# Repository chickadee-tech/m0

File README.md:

# Chickadee Tech M0 Polystack Control Board #
This control board features an ARM cortex M0 based SAMD21, the same chip as the Arduino Zero, and will be Arduino-compatible.

## Documentation ##
See the [wiki](https://github.com/chickadee-tech/m0/wiki) for documentation.

## Polystack ##
This **control** board is part of the Polystack platform for modular microcontrol systems. More information on the platform can be found at [polystack.org](http://polystack.org).

## Support ##
If you need support with a board you own or have development questions please email support@chickadee.tech or check [chickadee.tech/support](https://chickadee.tech/support) for other ways to get support.

## Contributing ##
Please note that this project is released with a [Contributor Code of Conduct](CODE_OF_CONDUCT.md). By participating in this project you agree to abide by its terms.

### Setup ###
Components and footprints for PCB parts are not included in this repository. Instead, checkout the [chickadee-tech/kicad-libs](https://github.com/chickadee-tech/kicad-libs) repository in the same directory that this repository is checked out in. All part definitions should be relative so that they will load correctly.

### Pull requests ###
For fixes please submit a pull request to the original repository. After the pull request is merged, check the [Chickadee Tech Active Contributor Discount (ACD)](https://chickadee.tech/active-contributor) to see if you are eligible for a discount code to use on your next purchase.

### Derivatives ###
If developing your own version of the M0 board please remove all Chickadee Tech trademarks and follow the [CC-BY license](LICENSE). While not required, please consider open sourcing your modifications so others can learn from your improvements. If you do email support@chickadee.tech and we may choose to add your project to the ACD.

You may also license the Polystack logo for free by emailing support@chickadee.tech. We'll ask for your gerbers to ensure the design complies with specifications laid out [here](https://github.com/chickadee-tech/polystack/wiki) and provide written permission to use the trademark after compliance has been demonstrated.

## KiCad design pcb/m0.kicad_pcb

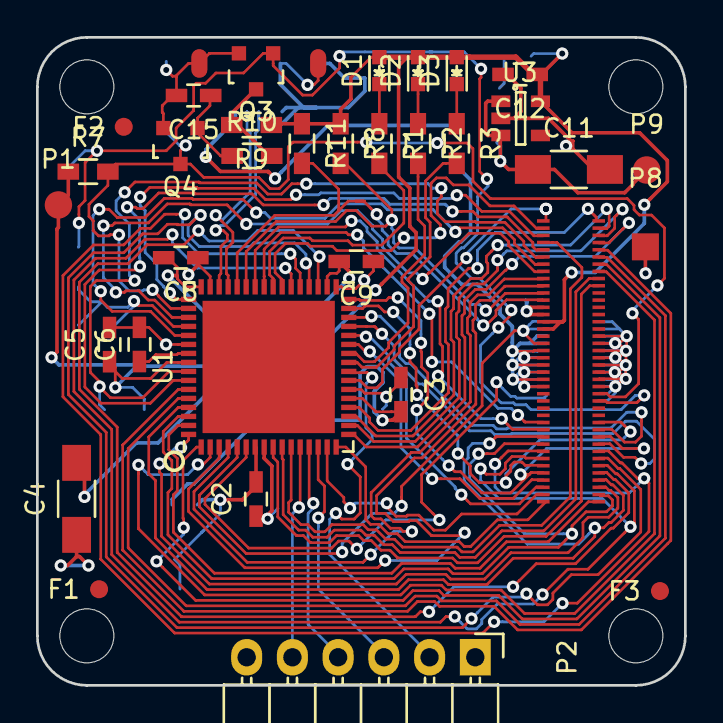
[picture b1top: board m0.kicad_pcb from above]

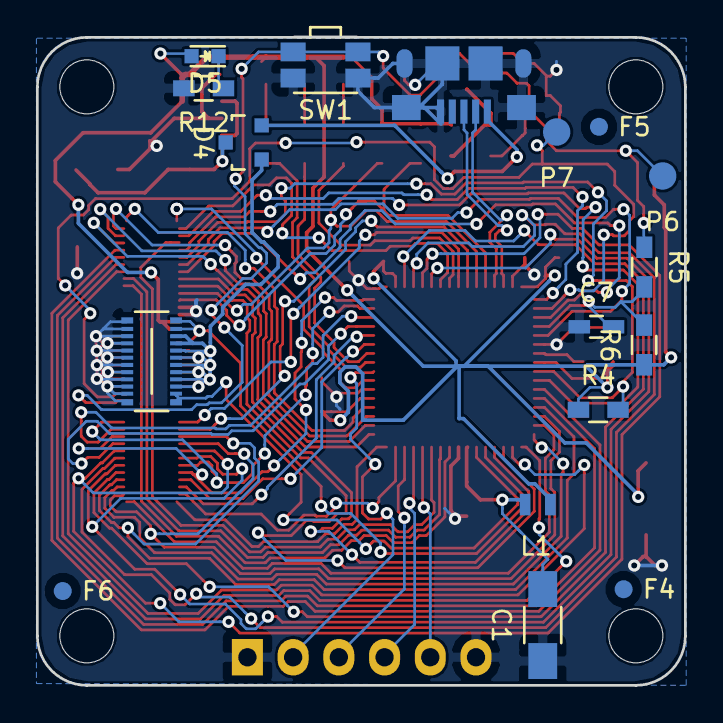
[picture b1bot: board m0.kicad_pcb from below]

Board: 2 copper layers, 36.0 x 36.0 mm, 50 parts (17 on the bottom side), 67 nets.

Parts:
C1, C4: 10uF; C_1206_HandSoldering
C2, C3, C5, C7, C8, C9: 0.1uF; C_0603_HandSoldering
C6: 1uF; C_0603_HandSoldering
C11: 10uF+; C_1206_HandSoldering
C12: 1uF+; C_0603_HandSoldering
C15: 2.2uF; C_0603_HandSoldering
D1: GREEN; LED_0603
D2: YELLOW; LED_0603
D3: RED; LED_0603
D4: D_Schottky_x2_KCom_AAK; SOT-23
D5: Red; LED_0603
F1, F2, F3, F4, F5, F6: 1mm; Fiducial
L1: INDUCTOR_SMALL; Neosid_Inductor_SM0603CG
P1: 3V3; Measurement_Point_Round-SMD-Pad_Small
P2: CONN_01X06; Pin_Header_Angled_1x06
P3: USB_OTG; Mini-USB-B-EDGE
P5: CONN_02X10; DF40-20pin-Header
P6: RESET; Measurement_Point_Round-SMD-Pad_Small
P7: BOOT0; Measurement_Point_Round-SMD-Pad_Small
P8: CONN_01X01; Measurement_Point_Square-SMD-Pad_Small
P9: 5V; Measurement_Point_Round-SMD-Pad_Small
PORT_OUT1: CKD_SANDWICH; DF40-3-4mm-80pin-Receptacle
Q3, Q4: Q_NMOS_GSD; SOT-23
R1, R2, R3, R4, R12: 1k; R_0603_HandSoldering
R5: 330; R_0603_HandSoldering
R6, R7: 10k; R_0603_HandSoldering
R8, R11: 2k; R_0603_HandSoldering
R9: 470k; R_0603_HandSoldering
R10: 100k; R_0603_HandSoldering
SW1: SW_PUSH; SW_SPST_EVQP7A
U1: SAMD21J; QFN-64-1EP_9x9mm_Pitch0.5mm
U3: TLV70233DBV; SOT-23-5

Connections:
+5V: D4.1, P5.3, P5.5, P5.7, P5.9, P5.11, P5.13, P5.15, P5.17, PORT_OUT1.19, PORT_OUT1.20, PORT_OUT1.21, PORT_OUT1.22, PORT_OUT1.23, PORT_OUT1.24
+5VA: D4.2, P3.1
+BATT: P5.19, PORT_OUT1.18, U1.5
/ADC1: PORT_OUT1.49, U1.10
/ADC2: PORT_OUT1.50, U1.9
/D0: P2.2, U1.24
/D1: P2.3, U1.14
/D2: P2.4, U1.13
/D3: P2.5, U1.12
/GPIO1: PORT_OUT1.5, U1.58
/GPIO2: PORT_OUT1.6, R4.2, U1.57
/GPIO3: PORT_OUT1.7, U1.53
/GPIO4: PORT_OUT1.8, U1.51
/GPIO5: PORT_OUT1.9, U1.4
/GPIO6: PORT_OUT1.10, U1.3
/LED1: R1.2, U1.40
/LED2: R2.2, U1.26
/LED3: R3.2, U1.25
/Power/CURRENT: P5.1, U1.6
/Reset/BOOT0: P7.1, PORT_OUT1.65, Q4.3, R7.2, U1.50
/Reset/RESET: P6.1, PORT_OUT1.66, Q3.1, R5.1, SW1.2
/SPI1_MOSI: PORT_OUT1.80, U1.63
/SPI1_SCK: PORT_OUT1.78, U1.64
/SPI2_MOSI: PORT_OUT1.76, U1.35
/SPI2_SCK: PORT_OUT1.74, U1.36
/SPI3_MOSI: PORT_OUT1.72, U1.29
/SPI3_SCK: PORT_OUT1.70, U1.30
/TIM1: PORT_OUT1.1, U1.23
/TIM2: PORT_OUT1.2, U1.39
/TIM3: PORT_OUT1.3, U1.49
/TIM4: PORT_OUT1.4, U1.11
/TIMG1_CH1: PORT_OUT1.41, U1.20
/TIMG1_CH2: PORT_OUT1.42, U1.19
/TIMG1_CH3: PORT_OUT1.43, U1.18
/TIMG1_CH4: PORT_OUT1.44, U1.17
/TIMG2_CH1: PORT_OUT1.45, U1.59
/TIMG2_CH2: PORT_OUT1.46, U1.60
/TIMG2_CH3: PORT_OUT1.47, U1.1
/TIMG2_CH4: PORT_OUT1.48, U1.2
/UART1_RX: PORT_OUT1.40, U1.16
/UART1_TX: PORT_OUT1.39, U1.15
/UART2_RX: PORT_OUT1.38, U1.28
/UART2_TX: PORT_OUT1.37, U1.27
/UART3_RX_SPI3_MISO: PORT_OUT1.36, PORT_OUT1.71, U1.32
/UART3_TX_SPI3_NSS: PORT_OUT1.35, PORT_OUT1.69, U1.31
/UART4_RX_SPI2_MISO: PORT_OUT1.34, PORT_OUT1.75, U1.38
/UART4_TX_SPI2_NSS: PORT_OUT1.33, PORT_OUT1.73, U1.37
/UART5_RX_SPI1_MISO: PORT_OUT1.32, PORT_OUT1.79, U1.62
/UART5_TX_SPI1_NSS: PORT_OUT1.31, PORT_OUT1.77, U1.61
/UART6_RX: PORT_OUT1.30, U1.42
/UART6_TX: PORT_OUT1.29, U1.41
/USB+: P3.3, U1.46
/USB-: P3.2, U1.45
/i2c_SCL: PORT_OUT1.12, R11.2, U1.44
/i2c_SDA: PORT_OUT1.11, R8.2, U1.43
GND: C1.1, C2.1, C3.1, C4.1, C5.2, C6.2, C7.1, C8.1, C9.1, C11.2, C12.2, C15.2, P2.1, P2.6, P3.5, P3.6, P5.2, P5.4, P5.6, P5.8, P5.10, P5.12, P5.14, P5.16, P5.18, P5.20, P8.1, PORT_OUT1.13, PORT_OUT1.14, PORT_OUT1.57, PORT_OUT1.58, PORT_OUT1.59, PORT_OUT1.60, PORT_OUT1.61, PORT_OUT1.62, PORT_OUT1.63, PORT_OUT1.64, Q3.2, Q4.2, R12.2, SW1.1, U1.8, U1.22, U1.33, U1.47, U1.54, U3.2
unnamed: C1.2, C2.2, L1.2, U1.7
unnamed: C6.1, U1.55
unnamed: C7.2, R5.2, R6.2, U1.52
unnamed: C11.1, D4.3, P9.1, U3.1, U3.3
unnamed: C15.1, Q4.1, R10.1
unnamed: D1.1, R1.1
unnamed: D2.1, R2.1
unnamed: D3.1, R3.1
unnamed: D5.1, R12.1
unnamed: Q3.3, R9.2, R10.2
VDD: C3.2, C4.2, C5.1, C8.2, C9.2, C12.1, D1.2, D2.2, D3.2, D5.2, L1.1, P1.1, PORT_OUT1.15, PORT_OUT1.16, R4.1, R6.1, R7.1, R8.1, R9.1, R11.1, U1.21, U1.34, U1.48, U1.56, U3.5

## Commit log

2016-04-16 Initial work on M0 control board.
2016-06-07 Finished trace routing.
2016-07-07 Add license information to many files. PCB design files are CC-BY and code is MIT license.
2016-07-07 Add back .gitignore after repo split.
2016-07-07 Convert to relative component and footprint paths.
2016-07-09 Add License, Code of Conduct and README.

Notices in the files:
pcb/m0.kicad_pcb:
Copyright 2016 Chickadee Tech LLC,
This work is licensed under the Creative Commons Attribution 4.0 International License.
To view a copy of this license, visit http://creativecommons.org/licenses/by/4.0
or send a letter to Creative Commons, PO Box 1866, Mountain View, CA 94042, USA.
